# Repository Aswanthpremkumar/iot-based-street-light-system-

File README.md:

View this project on [CADLAB.io](https://cadlab.io/project/29159). 

# iot-based-street-light-system-

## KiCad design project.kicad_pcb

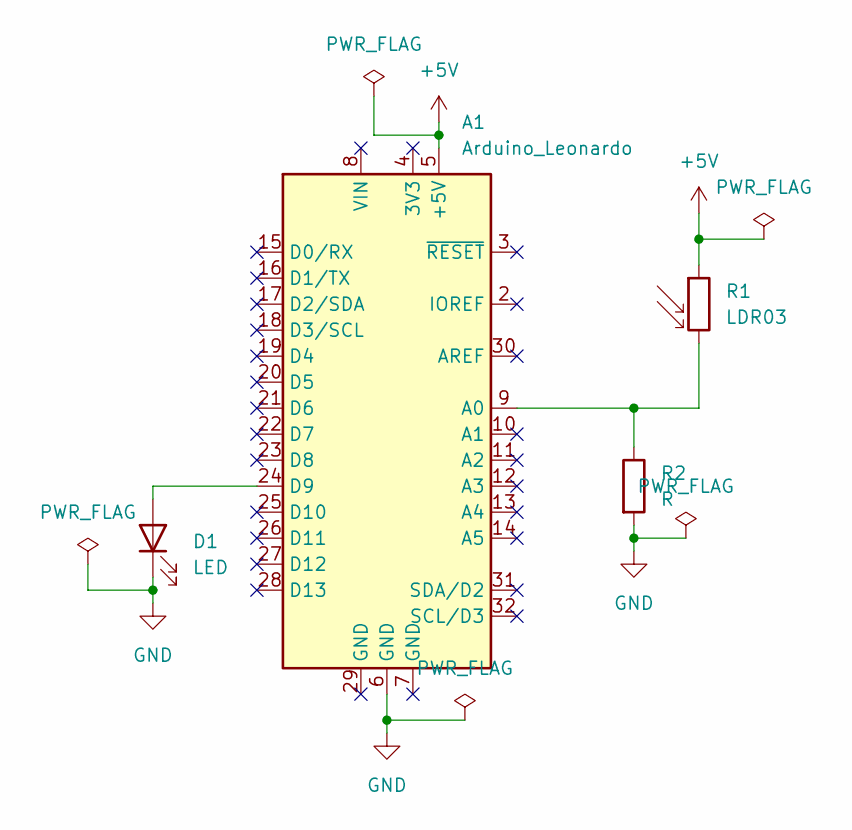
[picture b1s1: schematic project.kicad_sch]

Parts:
A1: Arduino_Leonardo; Arduino_UNO_R3
D1: LED; LED_0201_0603Metric
R1: LDR03; R_LDR_10x8.5mm_P7.6mm_Vertical
R2: R; R_LDR_4.9x4.2mm_P2.54mm_Vertical

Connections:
+5V: A1.5 (+5V), R1.1
GND: A1.6 (GND), D1.1 (K), R2.2
unnamed: A1.9 (A0), R1.2, R2.1
unnamed: A1.24 (D9), D1.2 (A)

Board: 2 copper layers, 4 parts (0 on the bottom side), 4 nets, no tracks yet.

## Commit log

2025-04-03 Backlink to CADLAB.io has been added.
